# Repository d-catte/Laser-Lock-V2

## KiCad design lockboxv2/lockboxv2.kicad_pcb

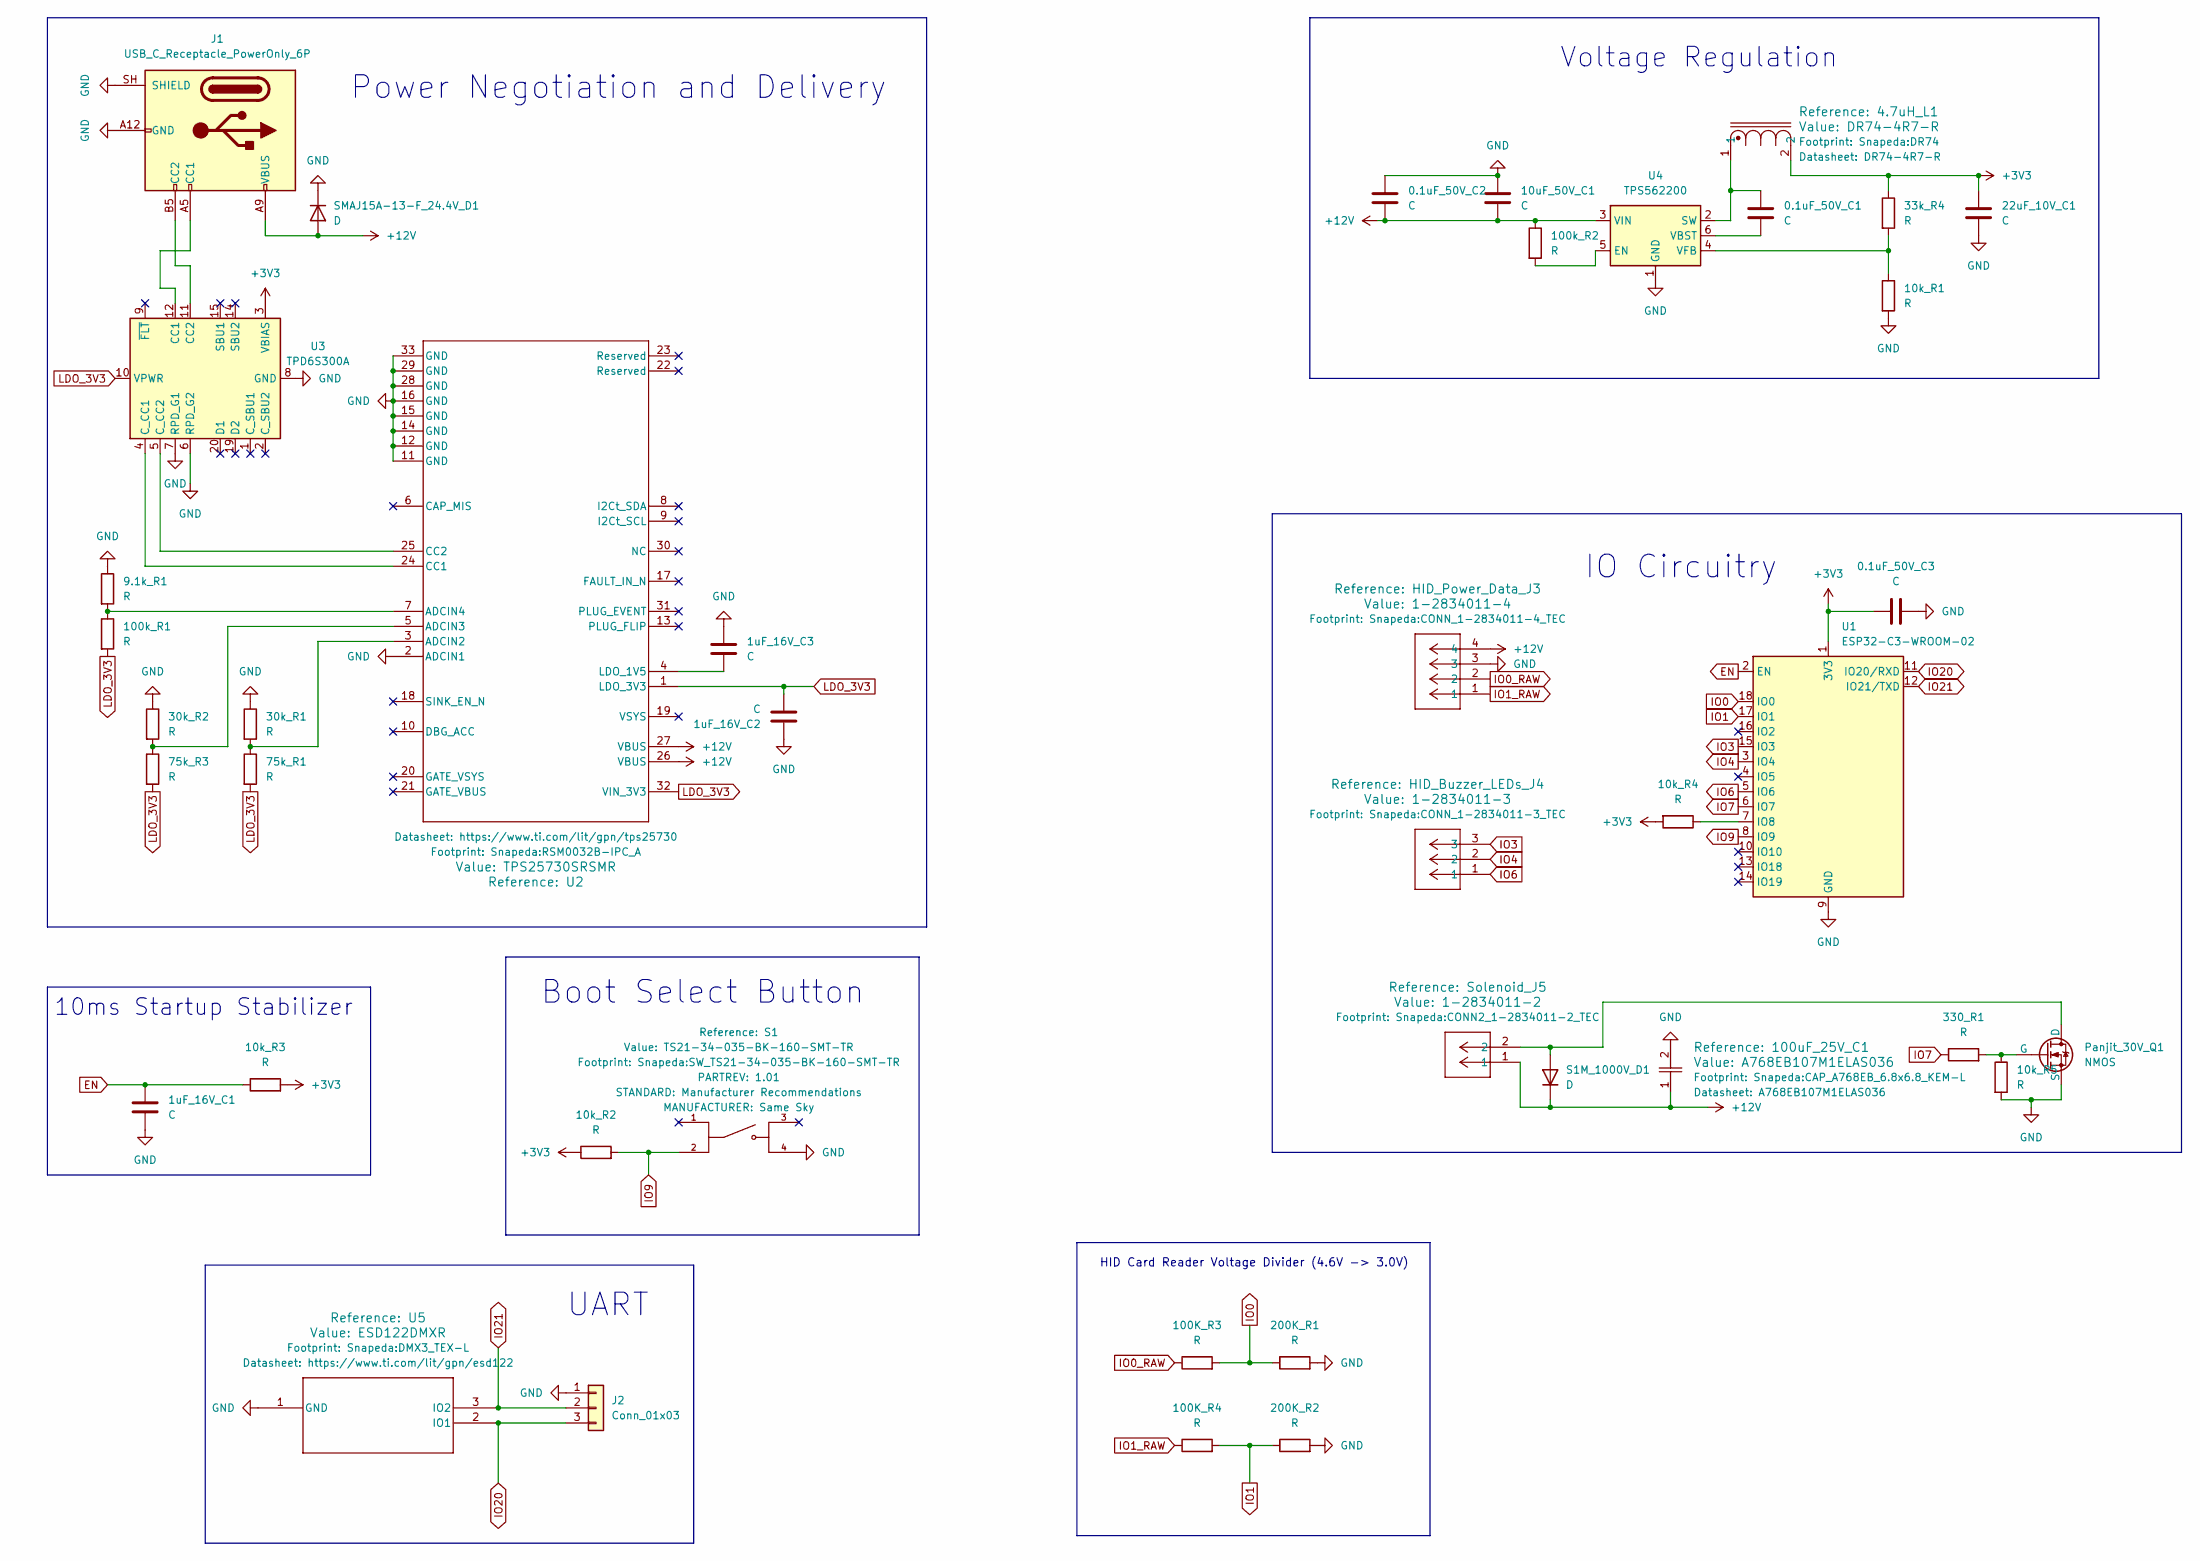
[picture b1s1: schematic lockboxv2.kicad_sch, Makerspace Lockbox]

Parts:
0.1uF_50V_C1, 0.1uF_50V_C2, 0.1uF_50V_C3, 22uF_10V_C1: C; C_0603_1608Metric
1uF_16V_C1, 1uF_16V_C2, 1uF_16V_C3: C; C_0402_1005Metric
4.7uH_L1: DR74-4R7-R; DR74
9.1k_R1, 10k_R1, 10k_R2, 10k_R3, 10k_R4, 10k_R5, 30k_R1, 30k_R2, 33k_R4, 75k_R1, 75k_R3, 100K_R3, 100K_R4, 100k_R1, 100k_R2, 200K_R1, 200K_R2, 330_R1: R; R_0402_1005Metric
10uF_50V_C1: C; C_1210_3225Metric
100uF_25V_C1: A768EB107M1ELAS036; CAP_A768EB_6.8x6.8_KEM-L
HID_Buzzer_LEDs_J4: 1-2834011-3; CONN_1-2834011-3_TEC
HID_Power_Data_J3: 1-2834011-4; CONN_1-2834011-4_TEC
J1: USB_C_Receptacle_PowerOnly_6P; USB_C_Receptacle_GCT_USB4125-xx-x-0190_6P_TopMnt_Horizontal
J2: Conn_01x03; PinHeader_1x03_P2.54mm_Vertical
Panjit_30V_Q1: NMOS; SOT-23
S1: TS21-34-035-BK-160-SMT-TR; SW_TS21-34-035-BK-160-SMT-TR; PARTREV 1.01
S1M_1000V_D1: D; D_SMA
SMAJ15A-13-F_24.4V_D1: D; D_SMA
Solenoid_J5: 1-2834011-2; CONN2_1-2834011-2_TEC
U1: ESP32-C3-WROOM-02
U2: TPS25730SRSMR; RSM0032B-IPC_A
U3: TPD6S300A; WQFN-20-1EP_3x3mm_P0.4mm_EP1.7x1.7mm_ThermalVias
U4: TPS562200; SOT-23-6
U5: ESD122DMXR; DMX3_TEX-L

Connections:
+3V3: 0.1uF_50V_C3.1, 4.7uH_L1.2, 10k_R2.1, 10k_R3.2, 10k_R4.2, 22uF_10V_C1.1, 33k_R4.1, U1.1 (3V3), U3.3 (VBIAS)
+12V: 0.1uF_50V_C2.2, 10uF_50V_C1.2, 100k_R2.1, 100uF_25V_C1.1, HID_Power_Data_J3.4, J1.A9 (VBUS), J1.B9 (VBUS), S1M_1000V_D1.1 (K), SMAJ15A-13-F_24.4V_D1.2 (A), Solenoid_J5.1, U2.26 (VBUS), U2.27 (VBUS), U4.3 (VIN)
EN: 1uF_16V_C1.1, 10k_R3.1, U1.2 (EN)
GND: 0.1uF_50V_C2.1, 0.1uF_50V_C3.2, 1uF_16V_C1.2, 1uF_16V_C2.1, 1uF_16V_C3.1, 9.1k_R1.1, 10k_R1.2, 10k_R5.2, 10uF_50V_C1.1, 22uF_10V_C1.2, 30k_R1.1, 30k_R2.1, 100uF_25V_C1.2, 200K_R1.2, 200K_R2.2, HID_Power_Data_J3.3, J1.A12 (GND), J1.B12 (GND), J1.SH (SHIELD), J2.1, Panjit_30V_Q1.3 (S), S1.4, SMAJ15A-13-F_24.4V_D1.1 (K), U1.9 (GND), U1.19 (GND), U2.2 (ADCIN1), U2.11 (GND), U2.12 (GND), U2.14 (GND), U2.15 (GND), U2.16 (GND), U2.28 (GND), U2.29 (GND), U2.33 (GND), U3.6 (RPD_G2), U3.7 (RPD_G1), U3.8 (GND), U3.13 (GND), U3.16 (GND), U3.17 (GND), U3.18 (GND), U3.21 (GND), U4.1 (GND), U5.1 (GND)
IO0: 100K_R3.2, 200K_R1.1, U1.18 (IO0)
IO0_RAW: 100K_R3.1, HID_Power_Data_J3.2
IO1: 100K_R4.2, 200K_R2.1, U1.17 (IO1)
IO1_RAW: 100K_R4.1, HID_Power_Data_J3.1
IO3: HID_Buzzer_LEDs_J4.3, U1.15 (IO3)
IO4: HID_Buzzer_LEDs_J4.2, U1.3 (IO4)
IO6: HID_Buzzer_LEDs_J4.1, U1.5 (IO6)
IO7: 330_R1.1, U1.6 (IO7)
IO9: 10k_R2.2, S1.2, U1.8 (IO9)
IO20: J2.3, U1.11 (IO20/RXD), U5.2 (IO1)
IO21: J2.2, U1.12 (IO21/TXD), U5.3 (IO2)
LDO_3V3: 1uF_16V_C2.2, 75k_R1.2, 75k_R3.2, 100k_R1.2, U2.1 (LDO_3V3), U2.32 (VIN_3V3), U3.10 (VPWR)
unnamed: J1.A5 (CC1), U3.12 (CC1)
unnamed: J1.B5 (CC2), U3.11 (CC2)
unnamed: Panjit_30V_Q1.1 (D), S1M_1000V_D1.2 (A), Solenoid_J5.2
unnamed: 10k_R5.1, 330_R1.2, Panjit_30V_Q1.2 (G)
unnamed: 10k_R4.1, U1.7 (IO8)
unnamed: 30k_R1.2, 75k_R1.1, U2.3 (ADCIN2)
unnamed: 30k_R2.2, 75k_R3.1, U2.5 (ADCIN3)
unnamed: 9.1k_R1.2, 100k_R1.1, U2.7 (ADCIN4)
unnamed: U2.24 (CC1), U3.4 (C_CC1)
unnamed: U2.25 (CC2), U3.5 (C_CC2)
unnamed: 1uF_16V_C3.2, U2.4 (LDO_1V5)
unnamed: 100k_R2.2, U4.5 (EN)
unnamed: 0.1uF_50V_C1.1, 4.7uH_L1.1, U4.2 (SW)
unnamed: 0.1uF_50V_C1.2, U4.6 (VBST)
unnamed: 10k_R1.1, 33k_R4.2, U4.4 (VFB)

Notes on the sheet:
UART
10ms Startup Stabilizer
HID Card Reader Voltage Divider (4.6V -> 3.0V)
Voltage Regulation
Power Negotiation and Delivery
Boot Select Button
IO Circuitry

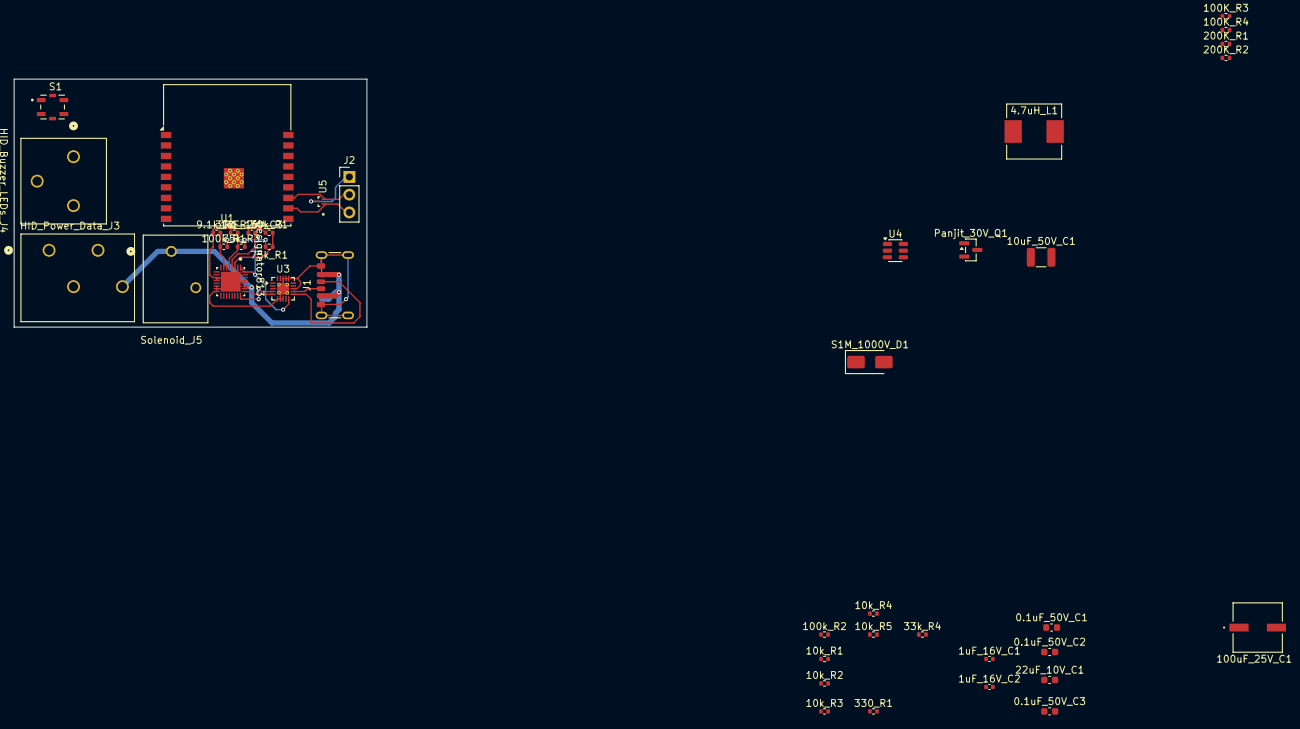
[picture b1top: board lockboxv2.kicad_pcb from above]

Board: 2 copper layers, 50.5 x 35.5 mm, 42 parts (1 on the bottom side), 31 nets.
